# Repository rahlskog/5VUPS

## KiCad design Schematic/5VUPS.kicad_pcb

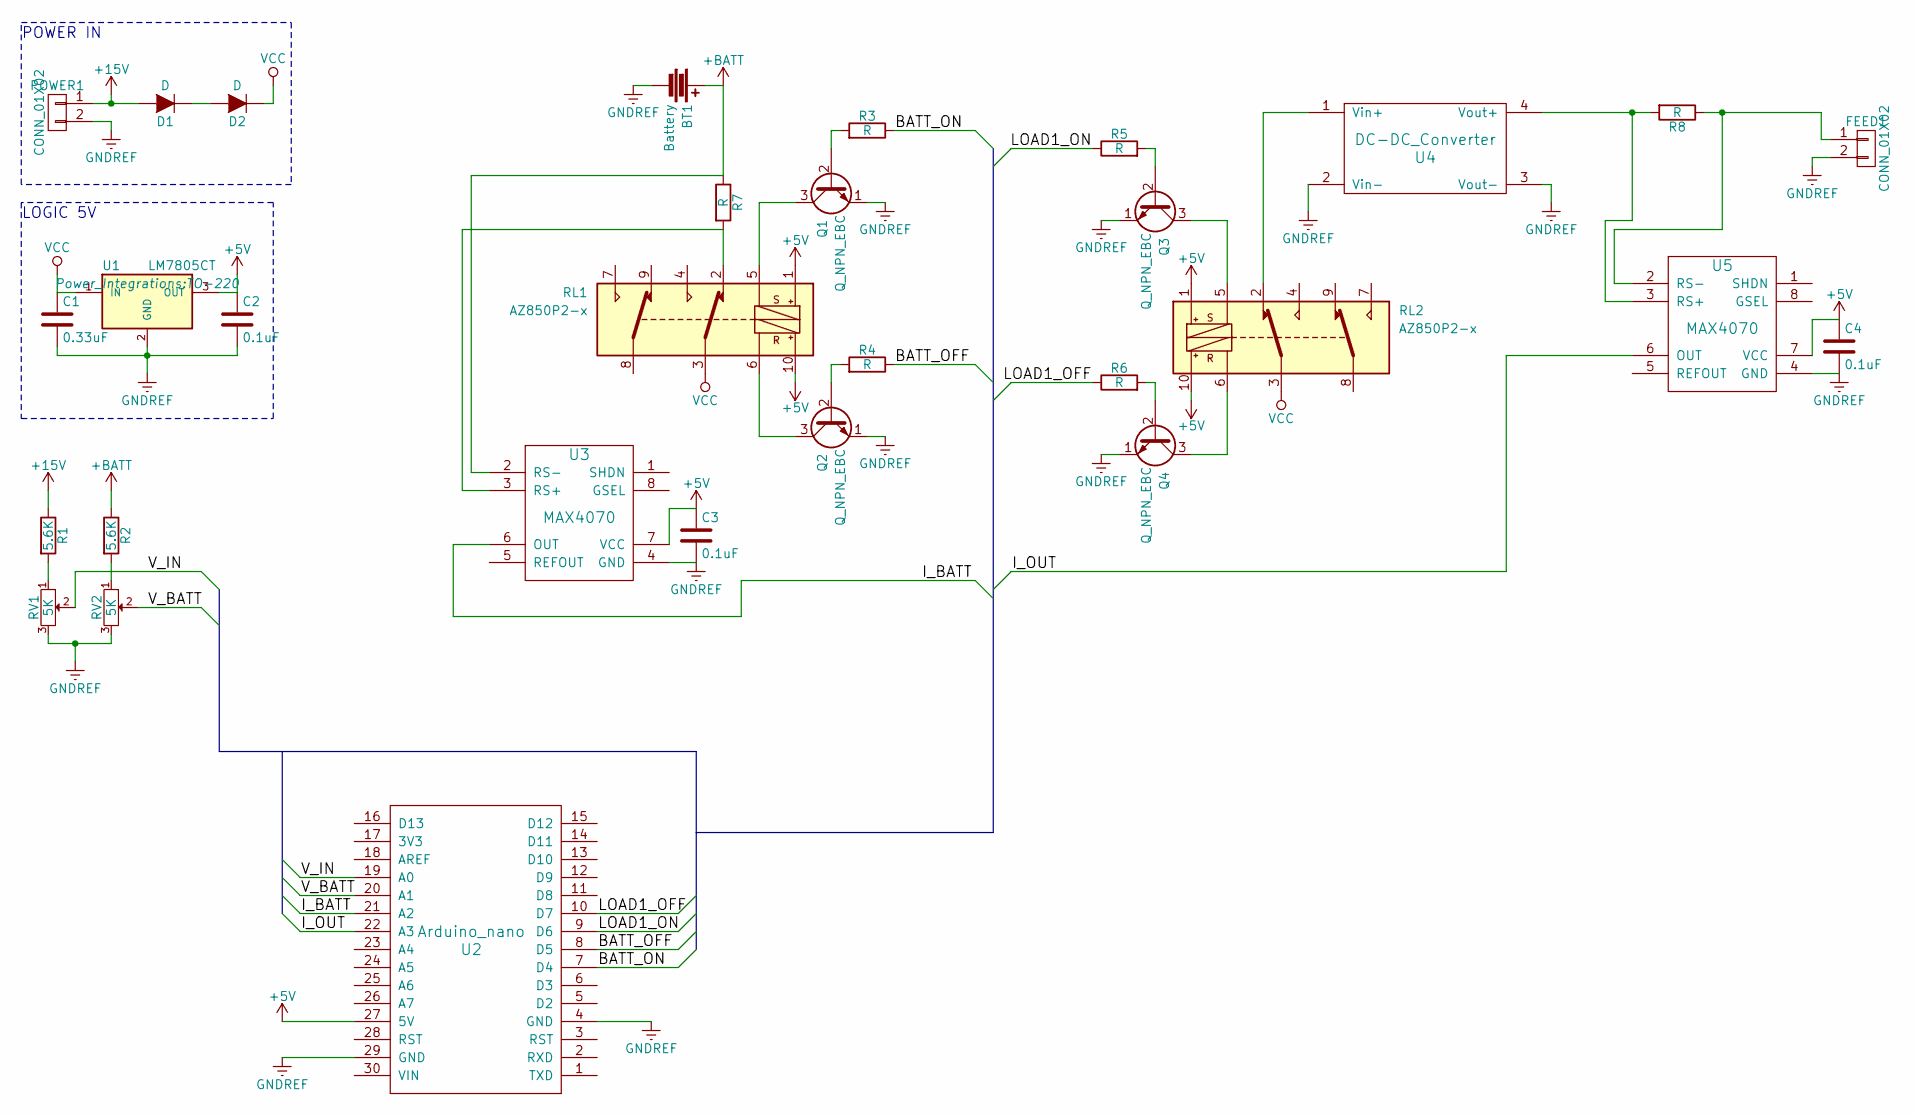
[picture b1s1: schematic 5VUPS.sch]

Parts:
BT1: Battery; AK300-2
C1: 0.33uF; C_Radial_D5_L11_P2
C2: 0.1uF; C_Disc_D3_P2.5
C3, C4: 0.1uF; C_0805_HandSoldering
D1, D2: D; Diode_DO-41_SOD81_Vertical_KathodeUp
FEED1: CONN_01X02; AK300-2
POWER1: CONN_01X02; AK300-2
Q1, Q2, Q3, Q4: Q_NPN_EBC; TO-92_Inline_Narrow_Oval
R1, R2: 5.6K; Resistor_Horizontal_RM7mm
R3, R4, R5, R6: R; Resistor_Horizontal_RM7mm
R7, R8: R; R_2010_HandSoldering
RL1, RL2: AZ850P2-x; DIP-10_W7.62mm_LongPads
RV1, RV2: 5K; Potentiometer_Bourns_3296W_3-8Zoll_Inline_ScrewUp
U1: LM7805CT; TO-220
U2: Arduino_nano
U3, U5: MAX4070; MSOP-8_3x3mm_Pitch0.65mm
U4: DC-DC_Converter; 20083_Adjustable_Power_Supply

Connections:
+5V: C2.1, C3.1, C4.1, RL1.1, RL1.10, RL2.1, RL2.10, U1.3 (OUT), U2.27 (5V), U3.7 (VCC), U5.7 (VCC)
+15V: D1.2 (A), POWER1.1, R1.1
+BATT: BT1.1, R2.1, R7.1, U3.2 (RS-)
/BATT_OFF: R4.1, U2.8 (D5)
/BATT_ON: R3.1, U2.7 (D4)
/I_BATT: U2.21 (A2), U3.6 (OUT)
/I_OUT: U2.22 (A3), U5.6 (OUT)
/LOAD1_OFF: R6.1, U2.10 (D7)
/LOAD1_ON: R5.1, U2.9 (D6)
/V_BATT: RV2.2, U2.20 (A1)
/V_IN: RV1.2, U2.19 (A0)
GNDREF: BT1.2, C1.2, C2.2, C3.2, C4.2, FEED1.2, POWER1.2, Q1.1 (E), Q2.1 (E), Q3.1 (E), Q4.1 (E), RV1.3, RV2.3, U1.2 (GND), U2.4 (GND), U2.29 (GND), U3.4 (GND), U4.2 (Vin-), U4.3 (Vout-), U5.4 (GND)
unnamed: D1.1 (K), D2.2 (A)
unnamed: FEED1.1, R8.1, U5.2 (RS-)
unnamed: Q1.2 (B), R3.2
unnamed: Q1.3 (C), RL1.5
unnamed: Q2.2 (B), R4.2
unnamed: Q2.3 (C), RL1.6
unnamed: Q3.2 (B), R5.2
unnamed: Q3.3 (C), RL2.5
unnamed: Q4.2 (B), R6.2
unnamed: Q4.3 (C), RL2.6
unnamed: R1.2, RV1.1
unnamed: R2.2, RV2.1
unnamed: R7.2, RL1.2, U3.3 (RS+)
unnamed: R8.2, U4.4 (Vout+), U5.3 (RS+)
unnamed: RL2.2, U4.1 (Vin+)
VCC: C1.1, D2.1 (K), RL1.3, RL2.3, U1.1 (IN)

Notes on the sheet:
POWER IN
LOGIC 5V

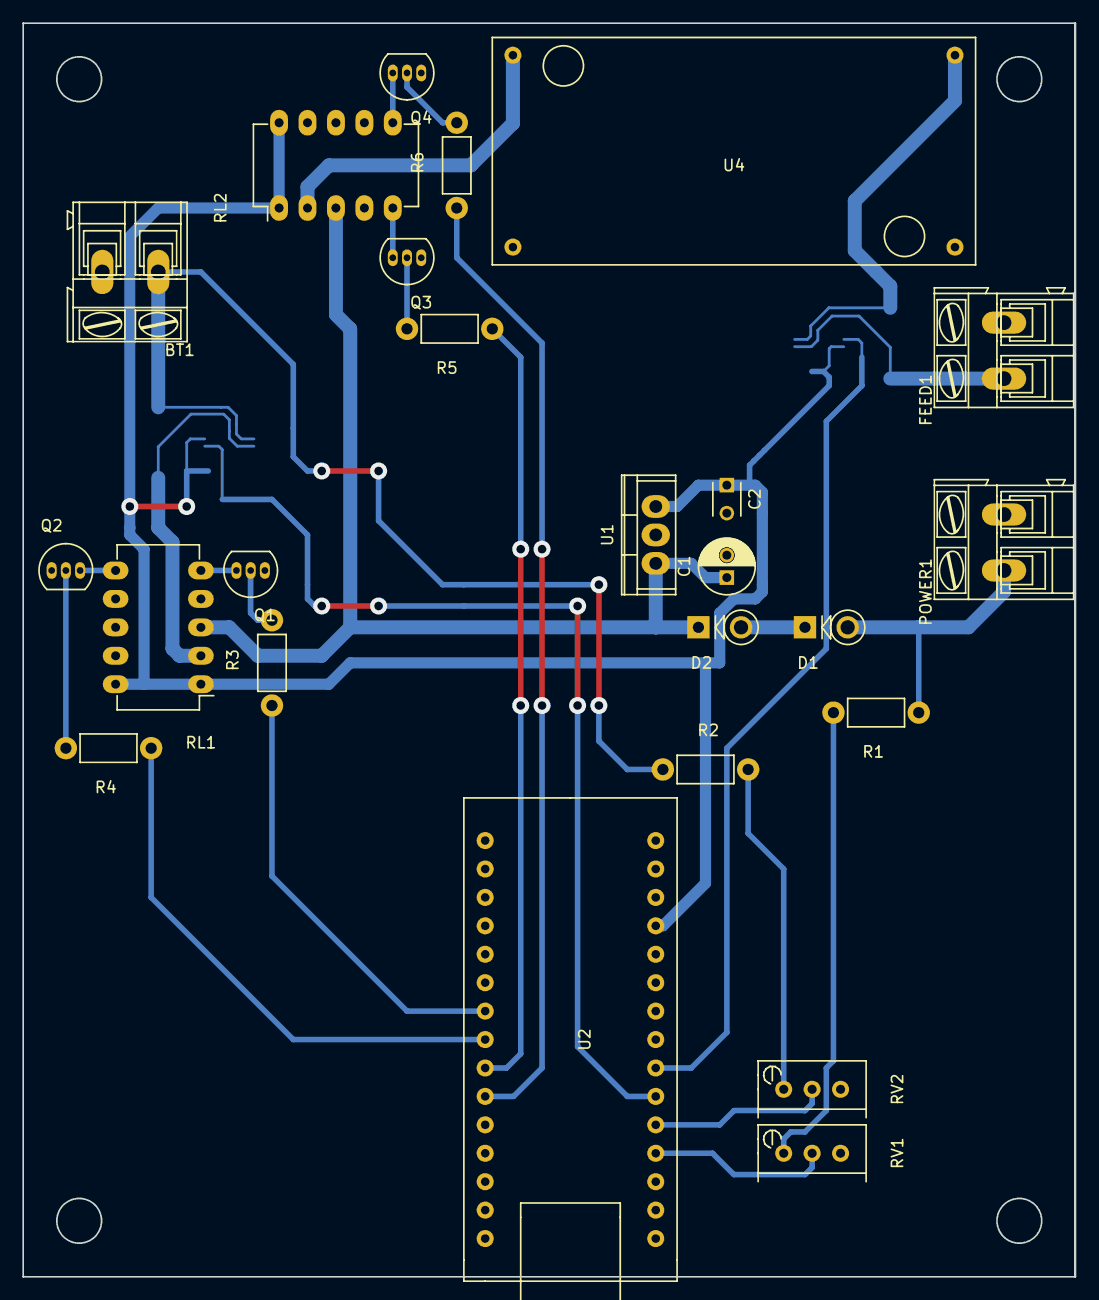
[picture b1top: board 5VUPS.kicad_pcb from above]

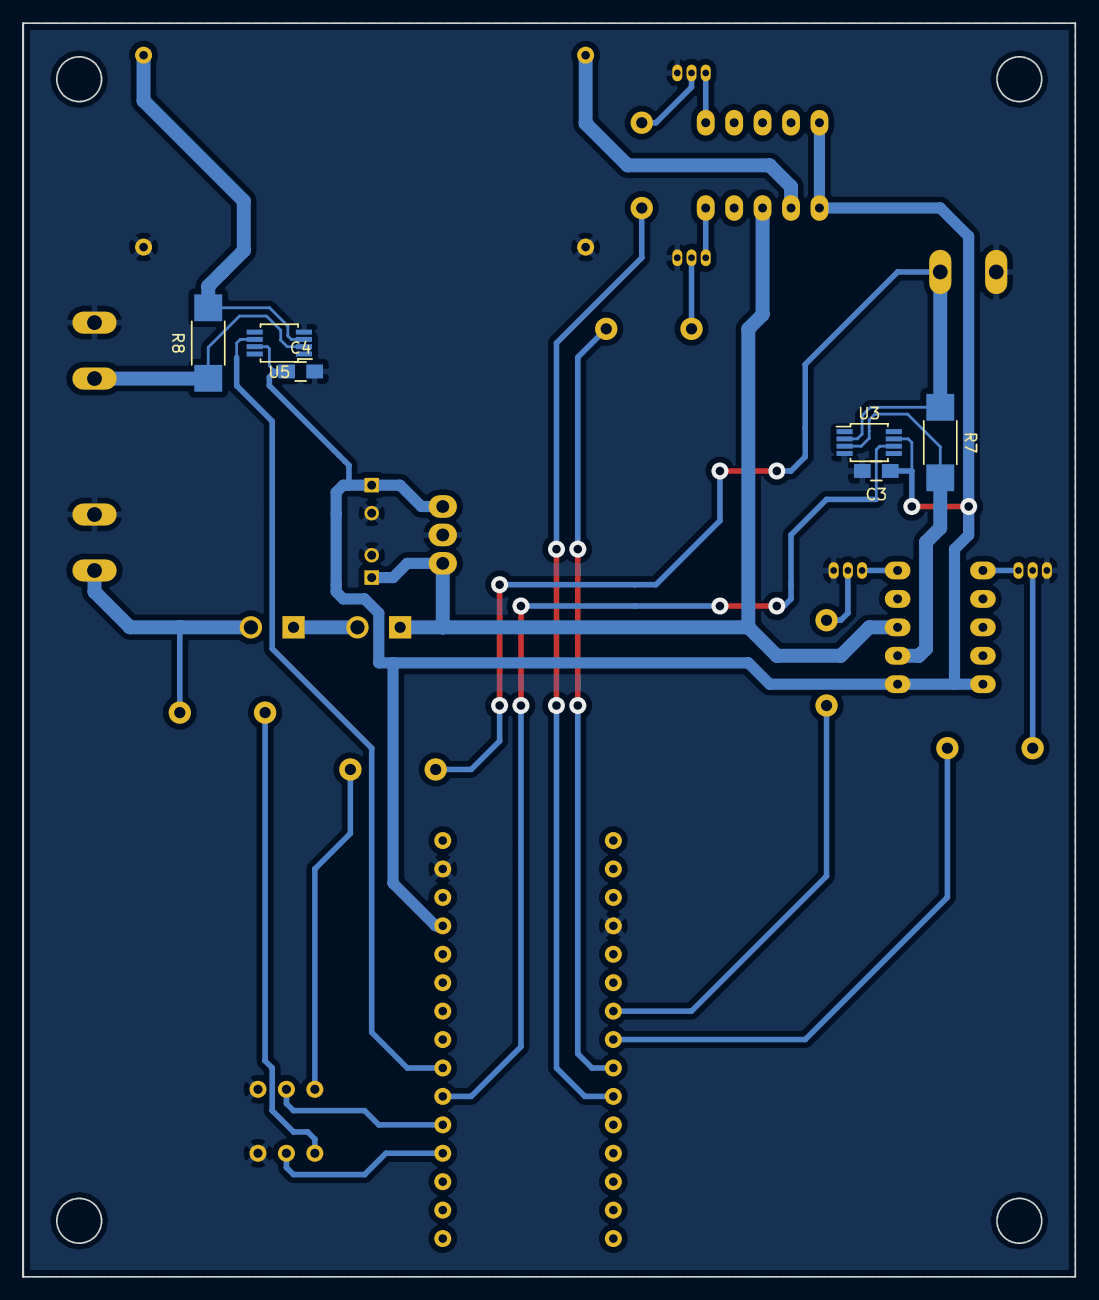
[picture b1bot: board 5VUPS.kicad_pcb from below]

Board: 2 copper layers, 94.0 x 112.0 mm, 30 parts (6 on the bottom side), 28 nets.

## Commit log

2016-05-31 Workset import
